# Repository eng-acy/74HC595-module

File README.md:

<h1 align="center">74HC595 Module</h1>

An 8-bit SIPO (Serial-In, Parallel-Out) shift register board for learning how the 74HC595 works.
**DATA IN**, **CLOCK**, **LATCH** and **CLEAR** are entered by hand with push buttons, and the eight outputs are shown on LEDs.
Boards can be chained through 6-Pin JST-XH connectors.

## Features
- 74HC595 (optional DIP-16 socket)
- 4 push buttons: **DATA IN**, **CLOCK**, **LATCH**, **CLEAR**, each with an indicator LED
- 8 output LEDs (O1–O8) plus a 01×08 header for the outputs
- USB-C 5V input (Power only) with a 0.5 A resettable PTC fuse and reverse-polarity clamp
- Chain IN / OUT on 6-Pin JST-XH: **+5V**, **RCLK**, **SRCLK**, **SRCLR**, **SER_IN/O8'**, **GND**

## Specifications
| Specification | Description |
|---|---|
| Board size | 100×62 mm, 04×M3 mounting holes |
| Layers | 2, GND pour on both sides |
| Power | 5V via USB-C, about 90 mA max per board |

## 3D View

## Repository contents
| Files / Folders | Description |
|---|---|
| [`74HC595-module.kicad_pro`](74HC595-module.kicad_pro) | KiCad 10 project (open this to open the entire project) |
| [`74HC595-module.kicad_sch`](74HC595-module.kicad_sch) | KiCad 10 schematic (open this to view only the schematic) |
| [`74HC595-module.kicad_pcb`](74HC595-module.kicad_pcb) | KiCad 10 pcb (open this to view only the pcb) |
| [`gerbers/`](gerbers/) | Gerber and drill files for manufacturing |
| [`documentation/`](documentation/) | Schematic PDF, Board Layout PDF, BOM, 3D Renders and GLB Model |
| [`3dmodels/`](3dmodels/) | Custom 3D models used by the board (Banded resistors, USB-C, Resettable PTC fuse) |

## Ordering the PCB
1. Zip the contents of [`gerbers/`](gerbers/) or download the Gerber zip from the [latest release](https://github.com/eng-acy/74HC595-module/releases/latest).
2. Upload it to a PCB fab (e.g. JLCPCB or PCBWay).
3. Options: 2 layers, 1.6 mm FR-4, HASL lead-free finish, any solder mask colour.

## Assembly
- Parts list: [`documentation/74HC595-module-BOM.csv`](documentation/74HC595-module-BOM.csv)
- The IC can be soldered directly to the board or you can also buy a **DIP-16 IC socket**, which isn't listed in the BOM.
- Solder the SMD parts first (J1 USB-C, F1, D1, D2, R1–R3, C1), then the through-hole parts from lowest to tallest.
- Check polarity on the diodes, LEDs and C2.

## How to use
1. Plug in USB-C. The green power LED (D1) should light up.
2. While holding **DATA IN** (1) or leaving it released (0), press **CLOCK** to shift the bit to the shift register. Repeat shifting bits as desired.
3. Press **LATCH** to store the shifted bits to the output register (O1–O8).
4. Press **CLEAR** to reset the shift register, then press **LATCH** to clear the output register.

## Built with
KiCad 10.0

## License
This work, including the KiCad design files, Gerber and drill files, documentation, renders and 3D models in this repository, is licensed under the
[Creative Commons Attribution-ShareAlike 4.0 International License (CC BY-SA 4.0)](https://creativecommons.org/licenses/by-sa/4.0/).

**You are free to:**
- **Share** – Copy and redistribute the material in any medium or format.
- **Adapt** – Remix, transform, and build upon the material for any purpose, even commercially.

**Under the following terms:**
- **Attribution** – You must give appropriate credit, provide a link to the license, and indicate if changes were made.
- **ShareAlike** – If you remix, transform, or build upon the material, you must distribute your contributions under the same license as the original.

You may share and adapt the design, including commercially, as long as you give credit and release your changes under the same license.

The full legal code is available at: [creativecommons.org/licenses/by-sa/4.0/legalcode](https://creativecommons.org/licenses/by-sa/4.0/legalcode)

See [`LICENSE`](LICENSE) for details.

## Author
<p align="left">
  <b>Adrian Christian Yap:</b>&emsp;
  <a href="https://www.linkedin.com/in/adrian-christian-yap-955712136/"><img align="absmiddle" height="28" alt="LinkedIn" src="https://img.shields.io/badge/LinkedIn-0A66C2?style=flat&logo=data%3Aimage%2Fsvg%2Bxml%3Bbase64%2CPHN2ZyB4bWxucz0iaHR0cDovL3d3dy53My5vcmcvMjAwMC9zdmciIHZpZXdCb3g9IjAgMCAyNCAyNCI%2BPHBhdGggZmlsbD0iI2ZmZmZmZiIgZD0iTTIwLjQ1IDIwLjQ1aC0zLjU2di01LjU3YzAtMS4zMy0uMDItMy4wNC0xLjg1LTMuMDQtMS44NSAwLTIuMTQgMS40NS0yLjE0IDIuOTR2NS42N0g5LjM0VjloMy40MXYxLjU2aC4wNWMuNDgtLjkgMS42NC0xLjg1IDMuMzctMS44NSAzLjYgMCA0LjI3IDIuMzcgNC4yNyA1LjQ2djYuMjh6TTUuMzQgNy40M2EyLjA2IDIuMDYgMCAxIDEgMC00LjEzIDIuMDYgMi4wNiAwIDAgMSAwIDQuMTN6TTcuMTIgMjAuNDVIMy41NlY5aDMuNTZ2MTEuNDV6Ii8%2BPC9zdmc%2B&logoColor=white"></a>
</p>
<p align="left">
  <b>MFI Polytechnic Institute:</b>&emsp;
  <a href="https://www.mfi.edu.ph/"><img align="absmiddle" height="28" alt="MFI Website" src="https://img.shields.io/badge/MFI_Polytechnic_Institute_Inc-1B3A8C?style=flat&logo=data%3Aimage%2Fpng%3Bbase64%2CiVBORw0KGgoAAAANSUhEUgAAABsAAAAcBAMAAABi%2F9neAAAAMFBMVEXv8vUAAACt3tOoq8yioqSVybjcqVxNZ59JWZghMIv8xl9bZaZlm6o7VJGzmXIlB7CrbJm3AAAAEHRSTlP%2BAP7%2B%2Ff7%2Bhln%2F%2F%2F%2Ftaf4XeZJDxQAAAVpJREFUeNpFjc8rg3EAh5%2Fv9%2F2O%2FWreNyFLvI2DX4dllOTwZrWy0%2B74B5S4uSAH4ihXpeWgOEgrzkuSQslBXN6mOSCxSWvyzuvA%2BNyenvo8wjvN38SqWNr8R21MCts27LuQYdghO5dSwMQ8%2BZqZswGAZYB9bYPAGp5LBWw01659%2BQCQQNlTRnYDoABm61NcBKqW2ywzv63l%2FyyeS5lScRXrJ67FovFK1UZM88cCWNLO5azqldb7BcGOKgaG%2Bs6z4ZHob3dQxQadSXRAuqCynw4cpwERfCfZYrX5bo5LaTUnHEVya%2BHaH7Eb08F30eTLJRtfSv633ZJpFtTHjuUEz%2FKVhsVrOk9l8YDTkXLEvB8uyK6CxlX4OeTOxp9fDnsyoLcdkdiToW1LZnUdQzgpLZE5yTMuhK6oa58i86RdjLfXCVfzicfbUfXwOdSzXvQiDNxi6%2BMiK%2FLVwP0GeYxtvRISp6MAAAAASUVORK5CYII%3D"></a>
  
  <a href="https://www.linkedin.com/school/mfi-polytechnic-institute-inc/home/"><img align="absmiddle" height="28" alt="LinkedIn" src="https://img.shields.io/badge/LinkedIn-0A66C2?style=flat&logo=data%3Aimage%2Fsvg%2Bxml%3Bbase64%2CPHN2ZyB4bWxucz0iaHR0cDovL3d3dy53My5vcmcvMjAwMC9zdmciIHZpZXdCb3g9IjAgMCAyNCAyNCI%2BPHBhdGggZmlsbD0iI2ZmZmZmZiIgZD0iTTIwLjQ1IDIwLjQ1aC0zLjU2di01LjU3YzAtMS4zMy0uMDItMy4wNC0xLjg1LTMuMDQtMS44NSAwLTIuMTQgMS40NS0yLjE0IDIuOTR2NS42N0g5LjM0VjloMy40MXYxLjU2aC4wNWMuNDgtLjkgMS42NC0xLjg1IDMuMzctMS44NSAzLjYgMCA0LjI3IDIuMzcgNC4yNyA1LjQ2djYuMjh6TTUuMzQgNy40M2EyLjA2IDIuMDYgMCAxIDEgMC00LjEzIDIuMDYgMi4wNiAwIDAgMSAwIDQuMTN6TTcuMTIgMjAuNDVIMy41NlY5aDMuNTZ2MTEuNDV6Ii8%2BPC9zdmc%2B&logoColor=white"></a>
</p>

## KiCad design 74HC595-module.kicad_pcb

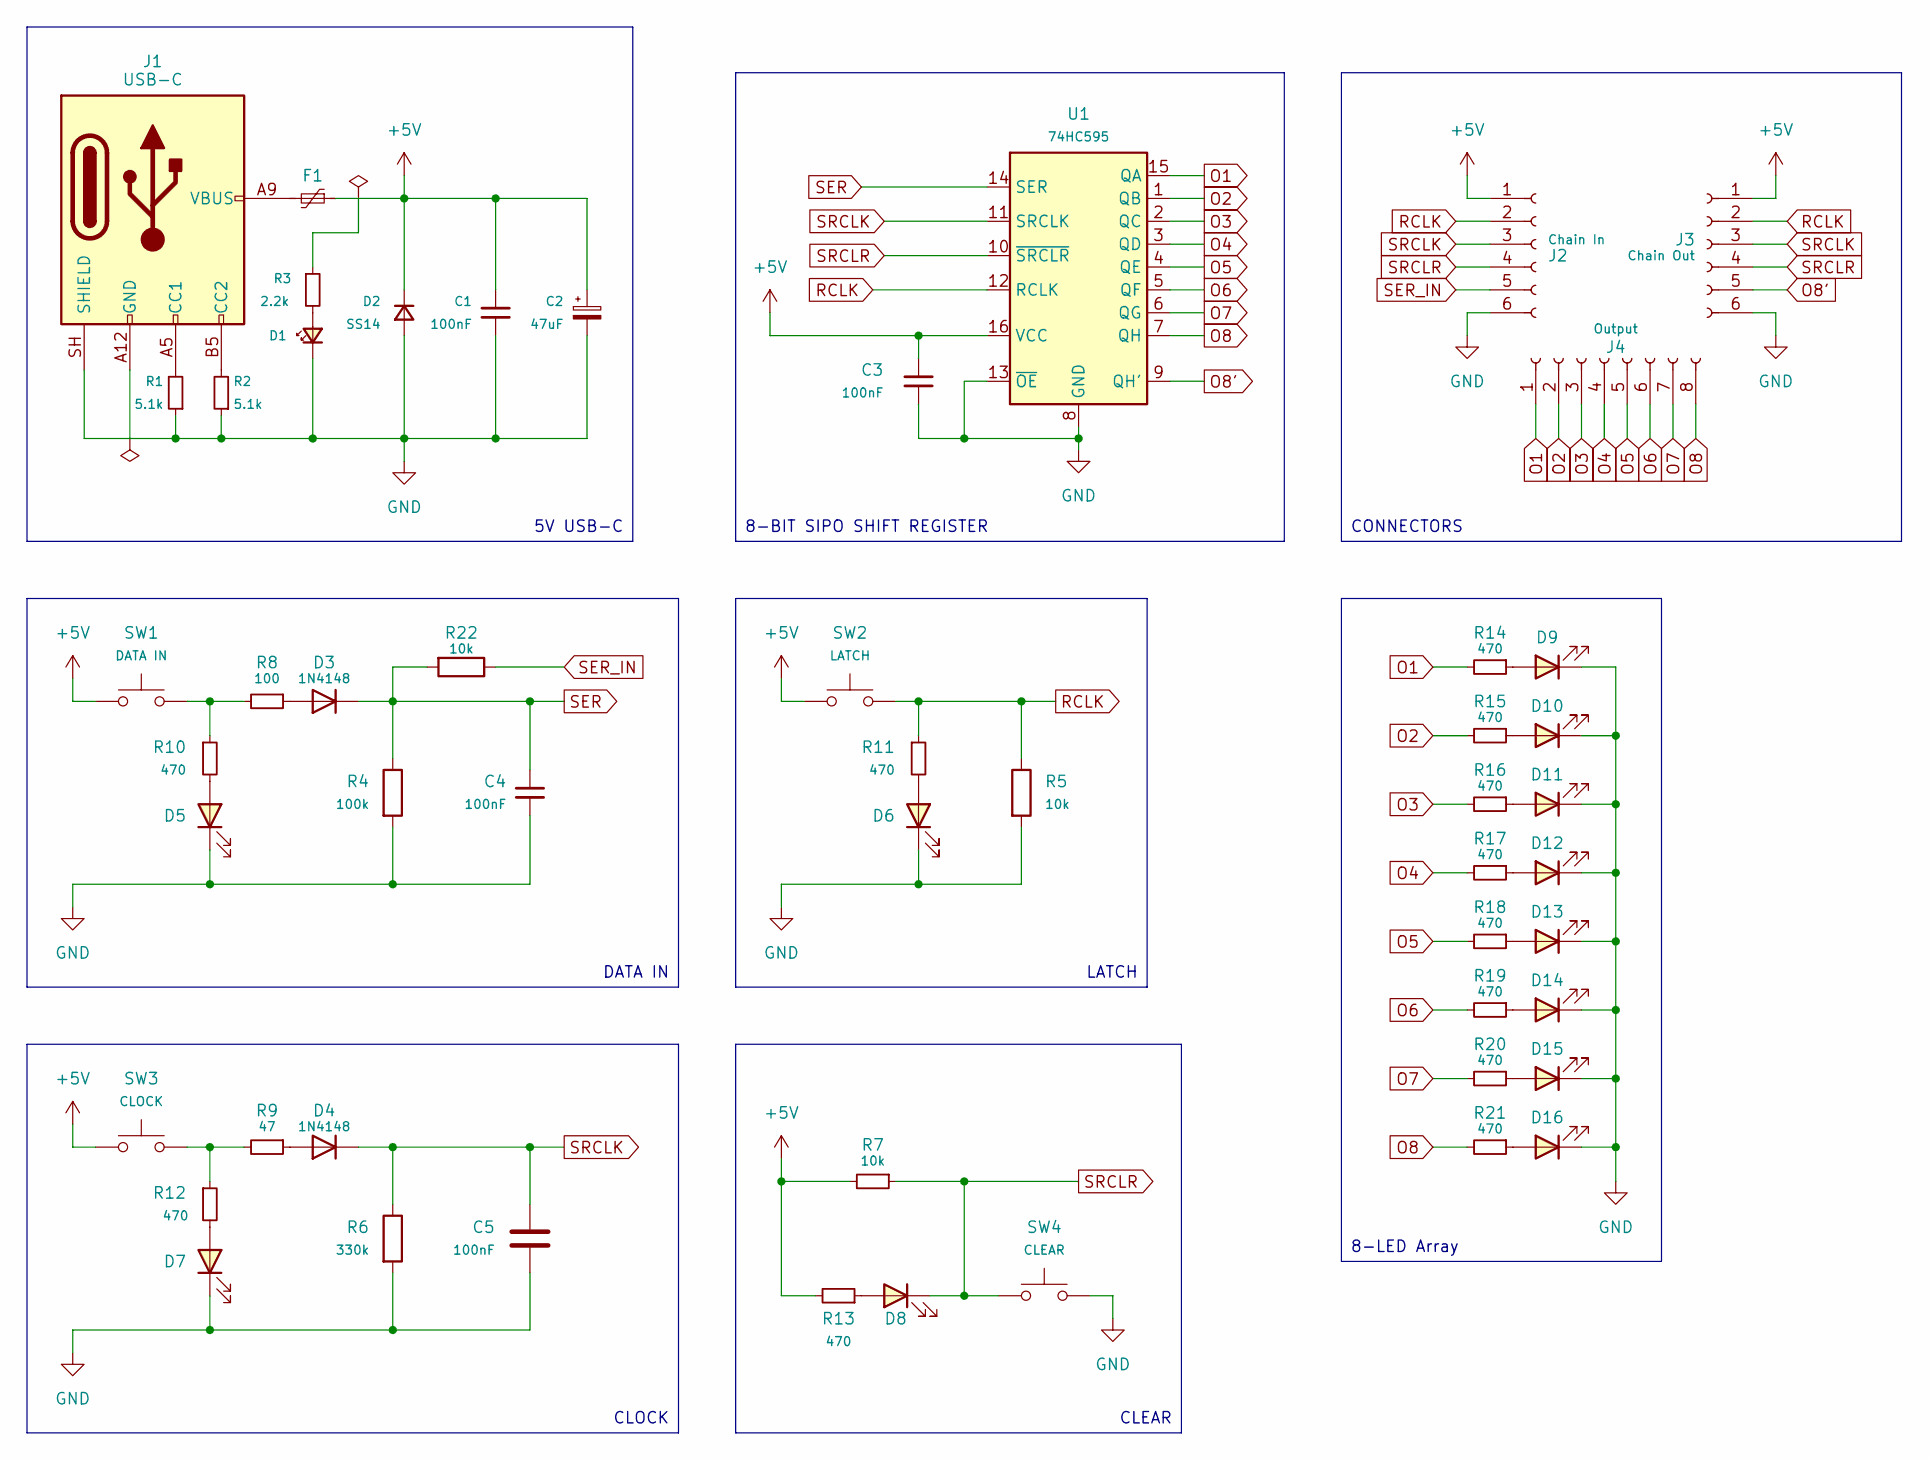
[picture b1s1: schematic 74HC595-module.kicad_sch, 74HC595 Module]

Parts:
C1: 100nF; C_0805_2012Metric_Pad1.18x1.45mm_HandSolder
C2: 47uF; CP_Radial_D5.0mm_P2.50mm
C3, C4, C5: 100nF; C_Disc_D5.0mm_W2.5mm_P5.00mm
D1: LED Green 0805; LED_0805_2012Metric_Pad1.15x1.40mm_HandSolder
D2: SS14; D_SMA_Handsoldering
D3, D4: 1N4148; D_DO-35_SOD27_P7.62mm_Horizontal
D5: LED Blue 3mm; LED_D3.0mm
D6: LED Green 3mm; LED_D3.0mm
D7: LED Yellow 3mm; LED_D3.0mm
D8: LED Red 3mm; LED_D3.0mm
D9, D10, D11, D12, D13, D14, D15, D16: LED Red 5mm; LED_D5.0mm
F1: MF-MSMF050-2; Fuse_1812_4532Metric_Pad1.30x3.40mm_HandSolder
J1: USB-C 6P; USB_C_Receptacle_HRO_TYPE-C-31-M-17
J2, J3: JST 01x06 2.5mm; JST_XH_B6B-XH-A_1x06_P2.50mm_Vertical
J4: Female Header 01x08 2.54mm; PinSocket_1x08_P2.54mm_Vertical
R1, R2: 5.1k; R_0805_2012Metric_Pad1.20x1.40mm_HandSolder
R3: 2.2k; R_0805_2012Metric_Pad1.20x1.40mm_HandSolder
R4: 100k; R_Axial_DIN0207_L6.3mm_D2.5mm_P10.16mm_Horizontal
R5, R7, R22: 10k; R_Axial_DIN0207_L6.3mm_D2.5mm_P10.16mm_Horizontal
R6: 330k; R_Axial_DIN0207_L6.3mm_D2.5mm_P10.16mm_Horizontal
R8: 100; R_Axial_DIN0207_L6.3mm_D2.5mm_P10.16mm_Horizontal
R9: 47; R_Axial_DIN0207_L6.3mm_D2.5mm_P10.16mm_Horizontal
R10, R11, R12, R13, R14, R15, R16, R17, R18, R19, R20, R21: 470; R_Axial_DIN0207_L6.3mm_D2.5mm_P10.16mm_Horizontal
SW1, SW2, SW3, SW4: NO Push Button 6mm; SW_PUSH_6mm
U1: 74HC595; DIP-16_W7.62mm_Socket

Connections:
+5V: C1.1, C2.1, C3.1, D2.1 (K), F1.1, J2.1, J3.1, R3.1, R7.2, R13.2, SW1.1, SW2.1, SW3.1, U1.16 (VCC)
GND: C1.2, C2.2, C3.2, C4.2, C5.2, D1.1 (K), D2.2 (A), D5.1 (K), D6.1 (K), D7.1 (K), D9.1 (K), D10.1 (K), D11.1 (K), D12.1 (K), D13.1 (K), D14.1 (K), D15.1 (K), D16.1 (K), J1.A12 (GND), J1.B12 (GND), J1.SH (SHIELD), J2.6, J3.6, R1.1, R2.1, R4.2, R5.2, R6.2, SW4.2, U1.8 (GND), U1.13 (~OE)
unnamed: D1.2 (A), R3.2
unnamed: D3.2 (A), R8.1
unnamed: D4.2 (A), R9.1
unnamed: D5.2 (A), R10.2
unnamed: D6.2 (A), R11.2
unnamed: D7.2 (A), R12.2
unnamed: D8.2 (A), R13.1
unnamed: D9.2 (A), R14.1
unnamed: D10.2 (A), R15.1
unnamed: D11.2 (A), R16.1
unnamed: D12.2 (A), R17.1
unnamed: D13.2 (A), R18.1
unnamed: D14.2 (A), R19.1
unnamed: D15.2 (A), R20.1
unnamed: D16.2 (A), R21.1
unnamed: F1.2, J1.A9 (VBUS), J1.B9 (VBUS)
unnamed: J1.A5 (CC1), R1.2
unnamed: J1.B5 (CC2), R2.2
unnamed: R8.2, R10.1, SW1.2
unnamed: R9.2, R12.1, SW3.2
O1: J4.1, R14.2, U1.15 (QA)
O2: J4.2, R15.2, U1.1 (QB)
O3: J4.3, R16.2, U1.2 (QC)
O4: J4.4, R17.2, U1.3 (QD)
O5: J4.5, R18.2, U1.4 (QE)
O6: J4.6, R19.2, U1.5 (QF)
O7: J4.7, R20.2, U1.6 (QG)
O8: J4.8, R21.2, U1.7 (QH)
O8': J3.5, U1.9 (QH')
RCLK: J2.2, J3.2, R5.1, R11.1, SW2.2, U1.12 (RCLK)
SER: C4.1, D3.1 (K), R4.1, R22.2, U1.14 (SER)
SER_IN: J2.5, R22.1
SRCLK: C5.1, D4.1 (K), J2.3, J3.3, R6.1, U1.11 (SRCLK)
SRCLR: D8.1 (K), J2.4, J3.4, R7.1, SW4.1, U1.10 (~SRCLR)

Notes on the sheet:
8-LED Array
CLOCK
5V USB-C
DATA IN
8-BIT SIPO SHIFT REGISTER
CONNECTORS
LATCH
CLEAR

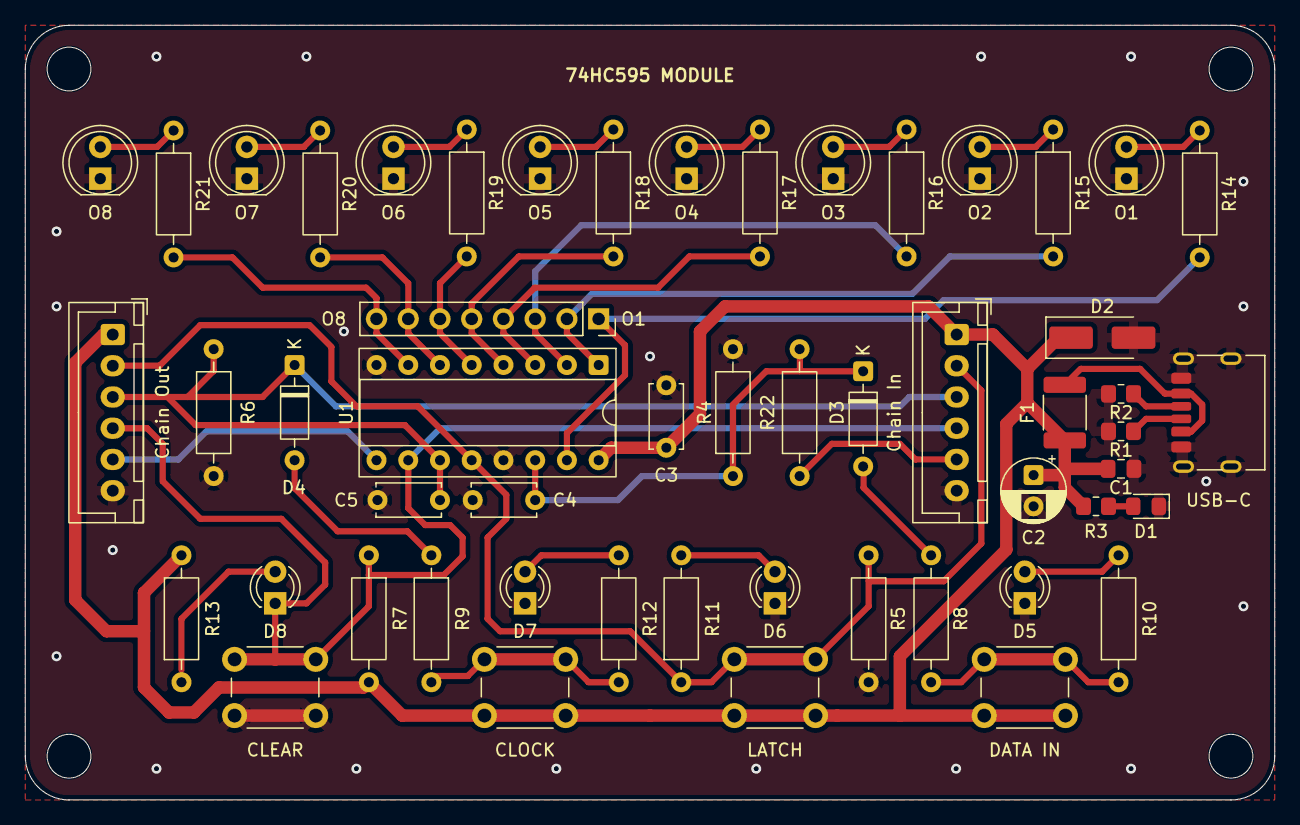
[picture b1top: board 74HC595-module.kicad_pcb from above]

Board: 2 copper layers, 100.0 x 62.0 mm, 58 parts (1 on the bottom side), 36 nets.

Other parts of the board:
H1, H2, H3, H4: MountingHole_3.5mm
LOGO: MFI; LOGO

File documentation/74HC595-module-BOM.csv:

Item,Qty,Reference,Value,Description,Footprint,Part Number,Datasheet
1,1,C1,100nF,"Unpolarized capacitor, small symbol",Capacitor_SMD:C_0805_2012Metric_Pad1.18x1.45mm_HandSolder,CL21B104KBCNNNC,
2,1,C2,47uF,"Polarized capacitor, small symbol",Capacitor_THT:CP_Radial_D5.0mm_P2.50mm,UVR1C470MDD,
3,3,C3-C5,100nF,"Unpolarized capacitor,Unpolarized capacitor, small symbol",Capacitor_THT:C_Disc_D5.0mm_W2.5mm_P5.00mm,K104K15X7RF53L2,
4,1,D1,LED Green 0805,"Green light emitting diode, small symbol",LED_SMD:LED_0805_2012Metric_Pad1.15x1.40mm_HandSolder,APT2012SGC,
5,1,D2,SS14,"Diode, small symbol",Diode_SMD:D_SMA_Handsoldering,SS14,
6,2,"D3,D4",1N4148,Diode,Diode_THT:D_DO-35_SOD27_P7.62mm_Horizontal,1N4148TR,
7,1,D5,LED Blue 3mm,Blue light emitting diode,LED_THT:LED_D3.0mm,WP710A10QBC/D,
8,1,D6,LED Green 3mm,Green light emitting diode,LED_THT:LED_D3.0mm,WP710A10GD,
9,1,D7,LED Yellow 3mm,Yellow light emitting diode,LED_THT:LED_D3.0mm,WP710A10YD,
10,1,D8,LED Red 3mm,Red light emitting diode,LED_THT:LED_D3.0mm,WP710A10ID,
11,8,D9-D16,LED Red 5mm,Red light emitting diode,LED_THT:LED_D5.0mm,WP7113ID,
12,1,F1,MF-MSMF050-2,"Resettable fuse, polymeric positive temperature coefficient, small symbol",Fuse:Fuse_1812_4532Metric_Pad1.30x3.40mm_HandSolder,MF-MSMF050-2,
13,1,J1,USB-C 6P,USB Power-Only 6P Type-C Receptacle connector,Connector_USB:USB_C_Receptacle_HRO_TYPE-C-31-M-17,TYPE-C-31-M-17,https://www.usb.org/sites/default/files/documents/usb_type-c.zip
14,2,"J2,J3",JST 01x06 2.5mm,"Generic connector, single row, 01x06, script generated",Connector_JST:JST_XH_B6B-XH-A_1x06_P2.50mm_Vertical,B6B-XH-A(LF)(SN),
15,1,J4,Female Header 01x08 2.54mm,"Generic connector, single row, 01x08, script generated",Connector_PinSocket_2.54mm:PinSocket_1x08_P2.54mm_Vertical,PPTC081LFBN-RC,
16,2,"R1,R2",5.1k,"Resistor, small symbol",Resistor_SMD:R_0805_2012Metric_Pad1.20x1.40mm_HandSolder,RC0805FR-075K1L,
17,1,R3,2.2k,"Resistor, small symbol",Resistor_SMD:R_0805_2012Metric_Pad1.20x1.40mm_HandSolder,RC0805FR-072K2L,
18,1,R4,100k,Resistor,Resistor_THT:R_Axial_DIN0207_L6.3mm_D2.5mm_P10.16mm_Horizontal,CFR-25JB-52-100K,
19,3,"R5,R7,R22",10k,"Resistor,Resistor, small symbol",Resistor_THT:R_Axial_DIN0207_L6.3mm_D2.5mm_P10.16mm_Horizontal,CFR-25JB-52-10K,
20,1,R6,330k,Resistor,Resistor_THT:R_Axial_DIN0207_L6.3mm_D2.5mm_P10.16mm_Horizontal,CFR-25JB-52-330K,
21,1,R8,100,"Resistor, small symbol",Resistor_THT:R_Axial_DIN0207_L6.3mm_D2.5mm_P10.16mm_Horizontal,CFR-25JB-52-100R,
22,1,R9,47,"Resistor, small symbol",Resistor_THT:R_Axial_DIN0207_L6.3mm_D2.5mm_P10.16mm_Horizontal,CFR-25JB-52-47R,
23,12,R10-R21,470,"Resistor, small symbol",Resistor_THT:R_Axial_DIN0207_L6.3mm_D2.5mm_P10.16mm_Horizontal,CFR-25JB-52-470R,
24,4,SW1-SW4,NO Push Button 6mm,"Push button switch, generic, two pins",Button_Switch_THT:SW_PUSH_6mm,B3F-1000,
25,1,U1,74HC595,8-bit serial in/out Shift Register 3-State Outputs,Package_DIP:DIP-16_W7.62mm_Socket,SN74HC595N,http://www.ti.com/lit/ds/symlink/sn74hc595.pdf
